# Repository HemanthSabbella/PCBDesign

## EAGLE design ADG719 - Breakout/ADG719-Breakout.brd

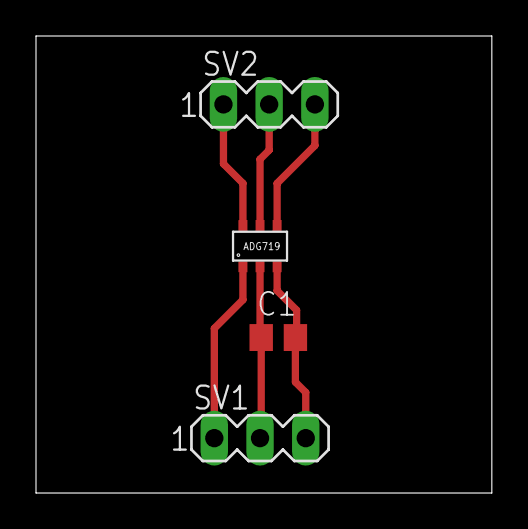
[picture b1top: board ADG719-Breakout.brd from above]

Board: 2 copper layers, 25.3 x 25.4 mm, 4 parts (0 on the bottom side), 6 nets.

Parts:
C1: 0.1uF; C0805
SV1, SV2: MA03-1
U$1: ADG719

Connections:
D_: SV2.2, U$1.5
GND: C1.2, SV1.3, U$1.3
IN_: SV1.1, U$1.1
S_1: SV2.3, U$1.4
S_2: SV2.1, U$1.6
VDD: C1.1, SV1.2, U$1.2

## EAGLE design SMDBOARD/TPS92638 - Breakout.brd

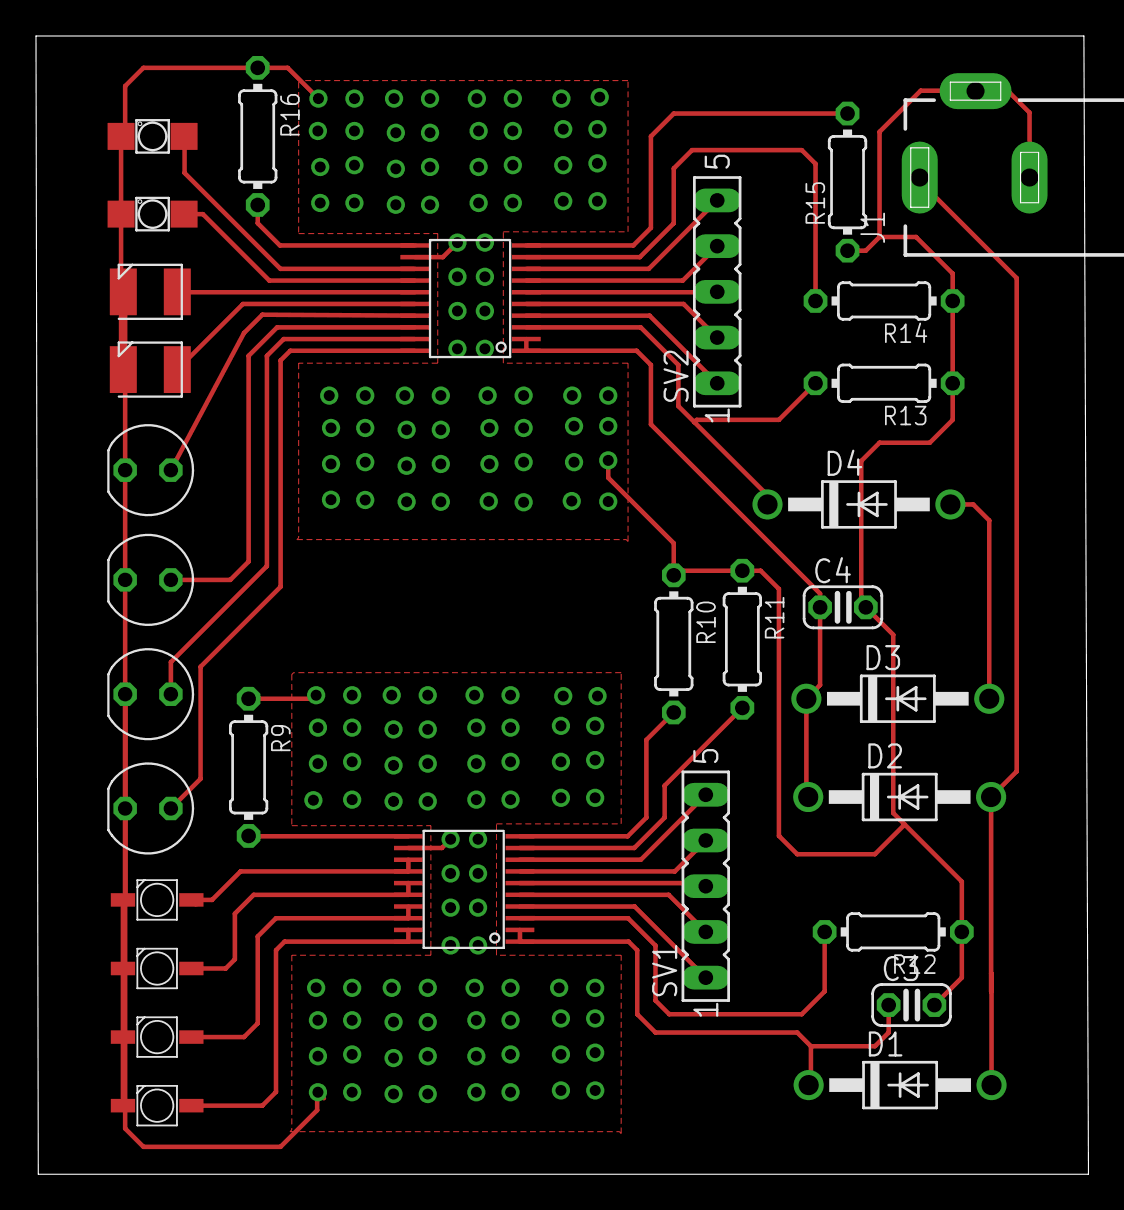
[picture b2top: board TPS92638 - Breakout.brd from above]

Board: 2 copper layers, 58.5 x 63.2 mm, 31 parts (0 on the bottom side), 35 nets.

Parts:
940NM1, 940NM2, 940NM3, 940NM4: VSMB2020; GULLWING-2.3MM
C3, C4: 0.1uF; C025-024X044
D1, D2, D3, D4: 1N4004; DO41-10
J1: DCJ0202
R9: 16k; 0204/7
R10: 7k; 0204/7
R11, R12, R13, R14, R15: 10k; 0204/7
R16: 49k; 0204/7
SV1, SV2: FE05-1
U$1, U$2: TPS92638
U$3, U$4: 1316
U$5, U$6: L424
U$7, U$8: LHT674
U$9, U$10: OSI-330_SERIES

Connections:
+12V: D1.A, D2.A, J1.1
GND: 940NM1.P$2, 940NM2.P$2, 940NM3.P$2, 940NM4.P$2, C3.2, C4.2, J1.2, J1.3, R9.1, R10.1, R11.1, R12.1, R13.1, R14.1, R15.1, R16.1, U$1.GND, U$2.GND, U$3.CATHODE, U$4.CATHODE, U$5.CATHODE, U$6.CATHODE, U$7.CATHODE, U$8.CATHODE, U$9.CATHODE, U$10.CATHODE
unnamed: SV1.1, U$1.PWM1
unnamed: SV1.2, U$1.PWM2
unnamed: SV1.3, U$1.PWM3
unnamed: SV1.4, U$1.PWM4
unnamed: R12.2, U$1.STOP
unnamed: SV2.1, U$2.PWM1
unnamed: SV2.2, U$2.PWM2
unnamed: SV2.3, U$2.PWM3
unnamed: SV2.4, U$2.PWM4
unnamed: D4.C, R13.2, U$2.STOP
unnamed: R10.2, U$1.REFHI
unnamed: R11.2, U$1.TEMP
unnamed: R9.2, U$1.REF
unnamed: R14.2, U$2.TEMP
unnamed: R15.2, U$2.REFHI
unnamed: R16.2, U$2.REF
unnamed: C3.1, D1.C, U$1.EN, U$1.SUPPLY
unnamed: C4.1, D2.C, D3.C, U$2.EN, U$2.SUPPLY
unnamed: 940NM1.P$1, U$1.IOUT1, U$1.IOUT2
unnamed: 940NM2.P$1, U$1.IOUT3, U$1.IOUT4
unnamed: U$2.IOUT1, U$3.ANODE
unnamed: 940NM3.P$1, U$1.IOUT5, U$1.IOUT6
unnamed: 940NM4.P$1, U$1.IOUT7, U$1.IOUT8
unnamed: U$2.IOUT2, U$4.ANODE
unnamed: U$2.IOUT3, U$5.ANODE
unnamed: U$2.IOUT4, U$6.ANODE
unnamed: U$2.IOUT5, U$7.ANODE
unnamed: U$2.IOUT6, U$8.ANODE
unnamed: U$2.IOUT7, U$9.ANODE
unnamed: U$2.IOUT8, U$10.ANODE
unnamed: SV1.5, U$1.~FAULT
unnamed: SV2.5, U$2.~FAULT
unnamed: D3.A, D4.A
